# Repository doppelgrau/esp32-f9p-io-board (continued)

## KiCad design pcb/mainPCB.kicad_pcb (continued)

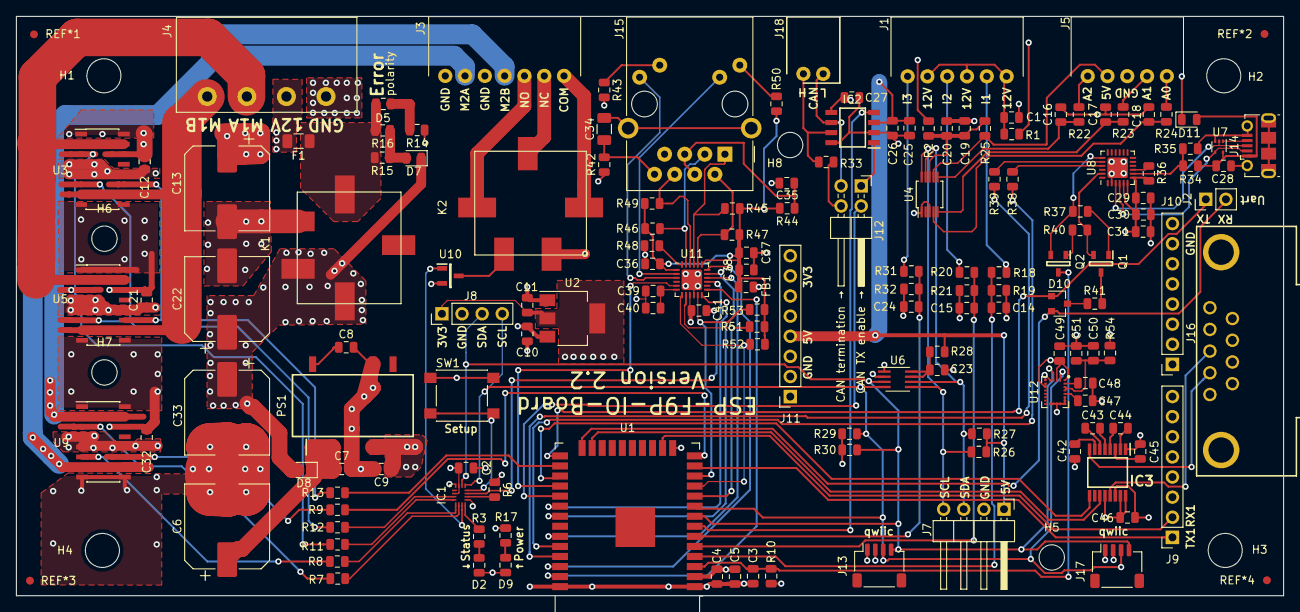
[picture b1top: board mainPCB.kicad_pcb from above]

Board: 4 copper layers, 160.0 x 73.2 mm, 158 parts (0 on the bottom side), 120 nets.

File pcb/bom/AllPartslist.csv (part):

Designator,Qty,MPN/Seeed SKU,type,value,detail,mouserNO.,DigikeyNO.,footprints
"C1, C3, C4, C2, C8, C12, C19, C21, C27, C26, C28, C30, C29, C32, C39, C41, C36, C38, C45, C44, C46, C43, C42, C51, C49, C48, C35",26,302010165,C,100n,Unpolarized capacitor,603-CC805KRX7R9BB104,,Capacitor_SMD:C_0805_2012Metric
"C5, C10, C11, C9, C20, C25, C37, ",7,302010171,C,22u,Unpolarized capacitor,963-LMK212BBJ226MG-T,,Capacitor_SMD:C_0805_2012Metric
"C6, C13, C22, C33, ",4,-,CP,560u,Polarized capacitor,647-UCM1V561MNL1GS ,,Capacitor_SMD:CP_Elec_10x10.5
"C7, C50, ",2,302010158,C,10u,Unpolarized capacitor,81-GRM21BR61E106MA3L,,Capacitor_SMD:C_0805_2012Metric
"C14, C15, C17, C18, C16, C23, C24, ",7,CL21C102JBCNNNC,C,1n,Unpolarized capacitor,710-885012207033,,Capacitor_SMD:C_0805_2012Metric
"C31, C40, ",2,302010148,C,2.2u,Unpolarized capacitor,963-LMK212BJ225KG-T,,Capacitor_SMD:C_0805_2012Metric
"C34, ",1,202R18W102KV4E,C,1n/2000V,Unpolarized capacitor,605-202R18W102KV4E,,Capacitor_SMD:C_1206_3216Metric
"C47, ",1,302010175,C,10n,Unpolarized capacitor,603-CC805KRX7R9BB103,,Capacitor_SMD:C_0805_2012Metric
"D2, ",1,304090039,LED,LED/yellow(origin blue),Light emitting diode,710-150080BS75000,,LED_SMD:LED_0805_2012Metric
"D5, ",1,304090046,LED,LED/red,Light emitting diode,710-150080VS75000,,LED_SMD:LED_0805_2012Metric
"D9, ",1,304090057,LED,LED/green,Light emitting diode,710-150080RS75000,,LED_SMD:LED_0805_2012Metric
"D7, D8, D11, ",3,SD0805S020S1R0,D,SD0805S020S1R0,Diode,581-SD0805S020S1R0,478-7800-1-ND,Diode_SMD:D_0805_2012Metric
"D10, ",1,BAT54CLT1G,BAT54C,BAT54C,"dual schottky barrier diode, common cathode",863-BAT54CLT1G,BAT54CFSCT-ND,Package_TO_SOT_SMD:SOT-23
"F1, ",1,3413.0329.22,Fuse,12A/slow,Fuse,693-3413.0329.22,486-1687-1-ND,ICs_own:Fuse_1206_3216Metric
"FB1, ",1,1-1624117-7,Ferrite_Bead,600R/2A,Ferrite bead,571-1-1624117-7,A102078CT-ND,Inductor_SMD:L_0805_2012Metric
"IC1, ",1,FXL6408UMX,FXL6408UMX,FXL6408UMX,Fully Configurable 8-Bit I2C-Controlled GPIO Expander,512-FXL6408UMX,FXL6408UMXCT-ND,ICs_own:QFN40P180X260X55-16N
"IC2, ",1,ATA6561-GAQW-N,ATA6561-GAQW-N,ATA6561-GAQW-N,"MICROCHIP - ATA6561-GAQW-N - CAN TRANSCEIVER, 5MBPS, -40 TO 150DEG C",579-ATA6561-GAQW-N,ATA6561-GBQW-NCT-ND,ICs_own:SOIC127P600X175-8N
"IC3, ",1,ICL3221EIVZ,ICL3221EIVZ-ND ,ICL3221EIVZ,"Intersil ICL3221EIVZ, Line Transceiver, EIA/TIA-232/ RS-232/ V.24/ V.28, 3.3 V, 5 V, 16-Pin TSSOP",968-ICL3221EIVZ,ICL3221EIVZ-ND,ICs_own:SOP65P640X120-16N
"J1, ",1,-,PTSM-Header-Horizontal-6,PTSM-Header-Horizontal-6,,651-1814883,277-9960-1-ND,Connector_own:1814883
"J3, ",1,-,PTSM-Header-Horizontal-7,PTSM-Header-Horizontal-7,,651-1814896,277-9961-1-ND,Connector_own:1814896
"J4, ",1,-,277-16334-ND ,CCA-Header-Horizontal-4,,651-1836366 ,277-16334-ND,Connector_own:1836366
"J5, ",1,-,PTSM-Header-Horizontal-5,PTSM-Header-Horizontal-5,,651-1814870,277-9959-1-ND,Connector_own:1814870
"J7, ",1,-,Conn_01x04_Male,Conn_01x04_Male,"Generic connector, single row, 01x04, script generated (kicad-library-utils/schlib/autogen/connector/)",649-68016-404HLF,,Connector_PinHeader_2.54mm:PinHeader_1x04_P2.54mm_Horizontal
"J8, ",1,-,Conn_01x04_Male,Conn_01x04_Male,"Generic connector, single row, 01x04, script generated (kicad-library-utils/schlib/autogen/connector/)",855-M20-9770446 ,,Connector_PinHeader_2.54mm:PinHeader_1x04_P2.54mm_Vertical
"J9, J10, J11, ",3,-,Conn_01x08_Female,Conn_01x08_Female,"Generic connector, single row, 01x08, script generated (kicad-library-utils/schlib/autogen/connector/)",855-M20-7820842,,Connector_PinSocket_2.54mm:PinSocket_1x08_P2.54mm_Vertical
"J12, ",1,-,Conn_02x02_Odd_Even,Conn_02x02_Odd_Even,"Generic connector, double row, 02x02, odd/even pin numbering scheme (row 1 odd numbers, row 2 even numbers), script generated (kicad-library-utils/schlib/autogen/connector/)",649-68021-404HLF,,Connector_PinHeader_2.54mm:PinHeader_2x02_P2.54mm_Horizontal
"J13, J17, ",2,-,SM04B-SRSS-TB(LF)(SN),SM04B-SRSS-TB(LF)(SN),"JST (JAPAN SOLDERLESS TERMINALS) - SM04B-SRSS-TB(LF)(SN) - CONNECTOR, HEADER, SMT, R/A, 1MM, 4WAY",474-PRT-14417,455-1804-1-ND,Connector_own:JST_SH_SM04B-SRSS-TB_1x04-1MP_P1.00mm_Horizontal
"J14, ",1,105017-0001,USB_B_Micro,USB_B_Micro,USB Micro Type B connector,538-105017-0001,WM1399CT-ND ,Connector_own:USB_Micro-B_Molex-105017-0001
"J15, ",1,-,RJ45_Amphenol_RJMG1BD3B8K1ANR,RJ45_Amphenol_RJMG1BD3B8K1ANR,"1 Port RJ45 Magjack Connector Through Hole 10/100 Base-T, AutoMDIX",523-RJMG1BD3B8K1ANR ,RJMG1BD3B8K1ANR-ND,Connector_own:RJ45_Amphenol_RJMG1BD3B8K1ANR
"J16, ",1,-,DB9_Male_MountingHoles,DB9_Male_MountingHoles,"9-pin male D-SUB connector, Mounting Hole",649-LD09P33E4GV00LF ,609-5186-ND,Connector_own:LD09P33E4GV00LF
"J18, ",1,-,PTSM-Header-Horizontal-2,PTSM-Header-Horizontal-2,,651-1814841,277-9956-1-ND,Connector_own:1814841
"K1, K2, ",2,-,CP1SA-12V-Z,CP1SA-12V-Z,"PANASONIC ELECTRIC WORKS - CP1SA-12V-Z - RELAY, AUTOMOTIVE, SPDT, 14VDC, 20A",769-CP1SA-12V-Z,255-3417-1-ND,Relay_own:CP1SA12VZ
"PS1, ",1,V78E05-1000-SMT-TR,V78E05-1000-SMT-TR,V78E05-1000-SMT-TR,,490-V78E05-1000SMTTR,102-5033-1-ND ,ICs_own:SOP254P1140X825-10N
"Q2, Q1, ",2,"BC817-40,215","BC817-40,215","BC817-40,215","BC817; BC817W; BC337 - 45 V, 500 mA NPN general-purpose transistors",771-BC817-40-T/R,1727-2919-1-ND,ICs_own:SOT95P230X110-3N
"R1, R25, R33, R39, R38, R41, ",6,301010351,R,120,Resistor,652-CR0805FX-1200ELF,,Resistor_SMD:R_0805_2012Metric
"R3, R17, ",2,CRCW0805620RFKEAC,R,620,Resistor,71-CRCW0805620RFKEAC,,Resistor_SMD:R_0805_2012Metric
"R10, R6, R18, R20, R24, R23, R22, R31, R35, ",9,CRCW080547K0FKEAC,R,47k,Resistor,71-CRCW080547K0FKEAC,,Resistor_SMD:R_0805_2012Metric
"R11, R12, R13, R7, R8, R9, R36, R37, R40, ",9,301010311,R,1k,Resistor,71-CRCW08051K00FKEAC,,Resistor_SMD:R_0805_2012Metric
"R14, R26, R27, R30, R29, R43, R50, R51, R52, R53, ",10,301012194,R,2.4k,Resistor,603-RC0805FR-072K4L,,Resistor_SMD:R_0805_2012Metric
"R2, R16, R15, R54, ",4,RC0805FR-0724RL,R,24,Resistor,603-RC0805FR-0724RL,,Resistor_SMD:R_0805_2012Metric
"R19, R21, R32, R48, ",4,RC0805FR-0712R1L,R,12.1k,Resistor,71-CRCW080512K1FKEAC,,Resistor_SMD:R_0805_2012Metric
"R28, ",1,RC0805FR-07220KL,R,220k,Resistor,652-CR0805JW-224ELF,,Resistor_SMD:R_0805_2012Metric
"R34, ",1,0805W8F2212T5E,R,22.1k,Resistor,652-CR0805FX-2212ELF,,Resistor_SMD:R_0805_2012Metric
"R42, R44, ",2,301011479,R,0,Resistor,603-RC0805JR-070RL,,Resistor_SMD:R_0805_2012Metric
"R45, R46, R47, R49, ",4,0805W8F499JT5E,R,49.9,Resistor,71-CRCW080549R9FKEAC,,Resistor_SMD:R_0805_2012Metric
"SW1, ",1,PTS645SM43SMTR92LFS,SW_Push,SW_Push,"Push button switch, generic, two pins",611-PTS645SM43SMTR92,CKN9112CT-ND,Button_Switch_SMD:SW_SPST_PTS645
"U1, ",1,ESP32-WROOM-32,ESP32-WROOM-32,ESP32-WROOM-32,"RF Module, ESP32-D0WDQ6 SoC, Wi-Fi 802.11b/g/n, Bluetooth, BLE, 32-bit, 2.7-3.6V, SMD",356-ESP-WROOM-32,1904-1023-1-ND ,RF_Module:ESP32-WROOM-32
"U2, ",1,AZ1117IH-3.3TRG1,AZ1117-3.3,AZ1117-3.3,"1A 20V Fixed LDO Linear Regulator, 3.3V, SOT-89/SOT-223/TO-220/TO-252/TO-263",621-AZ1117IH-3.3TRG1 ,AZ1117EH-3.3TRG1DICT-ND,Package_TO_SOT_SMD:SOT-223-3_TabPin2
"U3, U5, U9, ",3,VNH7070ASTR,497-17630-1-ND,VNH7070AS,The device is a full bridge motor driver intended for a wide range of automotive applications.,511-VNH7070ASTR,497-17630-1-ND,Package_SO:SOIC-16_3.9x9.9mm_P1.27mm
"U4, ",1,ADS1115IDGSR,ADS1115IDGS,ADS1115IDGS,"Ultra-Small, Low-Power, I2C-Compatible, 860-SPS, 16-Bit ADCs With Internal Reference, Oscillator, and Programmable Comparator, VSSOP-10",595-ADS1115IDGSR,296-38849-1-ND,Package_SO:MSOP-10_3x3mm_P0.5mm
"U6, ",1,PCA9306DCTR,PCA9306,PCA9306DCTR,Dual bidirectional I2C Bus and SMBus voltage level translator,595-PCA9306DCTR,296-18509-1-ND ,Package_SO:SSOP-8_2.95x2.8mm_P0.65mm
"U7, ",1,TPD3E001DRLR,TPD3E001DRLR,TPD3E001DRLR,TPD3E001 Low-Capacitance 3-Channel ESD-Protection for High-Speed Data Interfaces,595-TPD3E001DRLR,296-21885-1-ND,Package_TO_SOT_SMD:SOT-553
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
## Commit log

2019-03-17 first revision
2019-04-23 first version of the new feature set
2019-04-23 missing files added
2019-04-24 Added labels, added coper on the back to balance (avoid bending)
2019-04-24 fixed two vias (+5V instead of GND)
2019-04-25 Updated drill files with gerber - some missmatch had happend
2019-04-25 Changed some values - RC for the inputs to lower frequencys, reduced lines on the BOM by some minor value changes
2019-04-25 Addes schematics as pdf
2019-04-25 Started adding partnumbers from digikey
2019-04-30 Small optimization for soldermask
2019-05-02 A few more vias for the main 12V input (top layer -> third layer)
2019-05-12 changed soring of parts
2019-05-18 a quick and dirty test for iron compensationg in the LSM9DS1
2019-05-18 Changed Hardware-Test for the new board, not final
2019-05-18 cleanup
2019-05-18 added gyro calibration
2019-05-19 simplyfied gyro calibration
2019-05-19 Added CAN-Pins
2019-05-19 fixes for small Load-Test
2019-05-20 changed connection of the LAN8720A, RST to the FXL6408 and MDIO to the ESP32 (where RST was before). fixes #2
2019-05-20 changed some soldering pads to termal relief where no high current is expected. fixes #3
2019-05-20 removed the relais-error led
2019-05-20 fixed number of parts in the parts-List
2019-05-20 Moved the LSM9DS1 under F9P board, fixes #6
2019-05-20 Moved the USB and RS232 connectors a bit, more distance, so easier to use both at the same time
2019-05-20 Reduced the number of vias
2019-05-20 Removed 'internal soldering bridges' for easier inspection
2019-05-20 Minor cosmetic changes on tracks
2019-05-20 Moved Setup button switch. fixes #7
2019-05-22 Added five fiducials. fixes #3
2019-05-22 Moved mounting hole. fixes #1
2019-05-22 Minor cleanups
2019-05-23 Simplified some tracks
2019-05-23 Minor cosmetic changes, Added fiducials. fixes #4
2019-05-23 Changed Version on the Board
2019-05-23 Updated footprints of the SMT connectors, fixes #8. In addition simplified some tracks.
2019-05-23 Generated new gerber files. Fixes #9
2019-05-23 kicad updated some internal timestamps
2019-05-23 fixed 3d-references
2019-05-23 add rendering, add schematics as pdf
2019-05-23 Updated BOM/Part-List. Fixes #11
2019-05-25 Changed a bit the parameters for solderstop (increased min width to 0.15mm) and reduced a bit the padsize for the solderpaste-stecil (-2.5%)
2019-05-25 Updated gerber files
2019-05-30 Added an other uart for ardusimple RTK2Bligh daughterboard on top of the normal RTK2B. Removed two LEDs to free up PINs
2019-06-01 Minor cosmetic changes (moved some labels)
2019-06-01 Improved readme. Fixes #10
2019-06-03 Added fiducials (fixes #4), updated BOM, updated gerber files.
2019-07-11 helper for better manual pick & place
2019-07-11 a mostly self contained self test for the PCB, online some wireing in the plugs neccessary
2019-07-16 fixed copy and paste error in the parts.ods. Fixes #16
2019-07-21 make pickplacePDF, order CSV for 'www.seeedstudio.com'PCBA
    some files to order 'www.seeedstudio.com' PCB & PCB Assembly.
    Manufacturer Part Number(MPN) ,and DataSheet link list
2019-07-23 Update README.md
    Explained the shared pin layout of the rtk2blight uart (J2)
2019-07-23 Added BSD license
2019-07-24 Added code to test the CAN-bus interface with two PCBs (one DUT, one as CAN-Responder)
2019-07-24 Updated outdated rendering of the PCB
2019-08-05 a few clarifications regarding the pinout in the Readme
2019-08-05 Fixed #3 thermal relief pads. Removed an unwanted bridge between the ground planes
2019-08-06 Pull FORCEON to high on RS232 to avoid standby, fixed #18. Also implemented virtual symbol for permanent fiducials
2019-08-23 Removed inductor in front of ADS1115, replaced with resistor (RC should be enough, comparison with the RC on the LSM9DS1 did not show many differences)
2019-08-24 Edited some footprints (connectors, fxl6408). Fixes #19
2019-08-24 Changed a capacitor in the power supply (10u to 22u) for more capacity/stability
2019-08-24 Turned some Labels for the User, so he can read them with the ESP on top
2019-08-25 Update of gerber files, ibom, rendering, printed schematics, files for seedstudio
2019-08-26 Added a alternative Part number
2019-08-26 Added a better capacitor
2019-09-07 Removed center to avoid drilling at some manufactures
2019-09-07 Updated gerber
2019-09-22 Update README.md
    closes #29
    Thanks for the hint.
2019-10-06 First try of a case
2019-10-10 Fixed different mistakes
2019-10-26 AG_NTRIP_ESP.ino for ESP-F9P-IO-BOARD
    add IMU LSM9DS1 Inclinometer
    use status LED and setup SW
2019-10-31 Autosteer_ESP.ino for ESP-F9P-IO-BOARD
    add IMU LSM9DS1 Inclinometer
    MotorDriver VNH7070
2019-11-07 Changed the HW-Test. Less manual intervention, no external network connection required (only a second known good pcb), test the IMU
2019-11-07 Mechanical parts for the Test Setup
2019-11-07 Minor Adjustments for the USB/RS232 openings
2019-11-07 Rename Case
2019-11-07 Switched to 3mm screws, fixes #30
2019-11-07 two small holder and a bit more space for cable management, fixes #32 and fixes #31
2019-11-10 Added a 45° angle to the outside corner, moved the USB/RS232 cut a bit for better fitting the pcb
2019-11-10 Added a small support for the top
2019-11-11 Made the thinner/transparent parts a little bit thinner
2019-11-24 Fixed typo in the port numbering
